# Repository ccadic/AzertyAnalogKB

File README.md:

# AzertyAnalogKB
Analogic Azerty Keyboard
KICAD Files

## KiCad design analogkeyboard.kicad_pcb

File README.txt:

Source of inspiration 
https://twitter.com/technoblogy/status/1015229517068152832

Link to source files
http://www.technoblogy.com/show?28WK

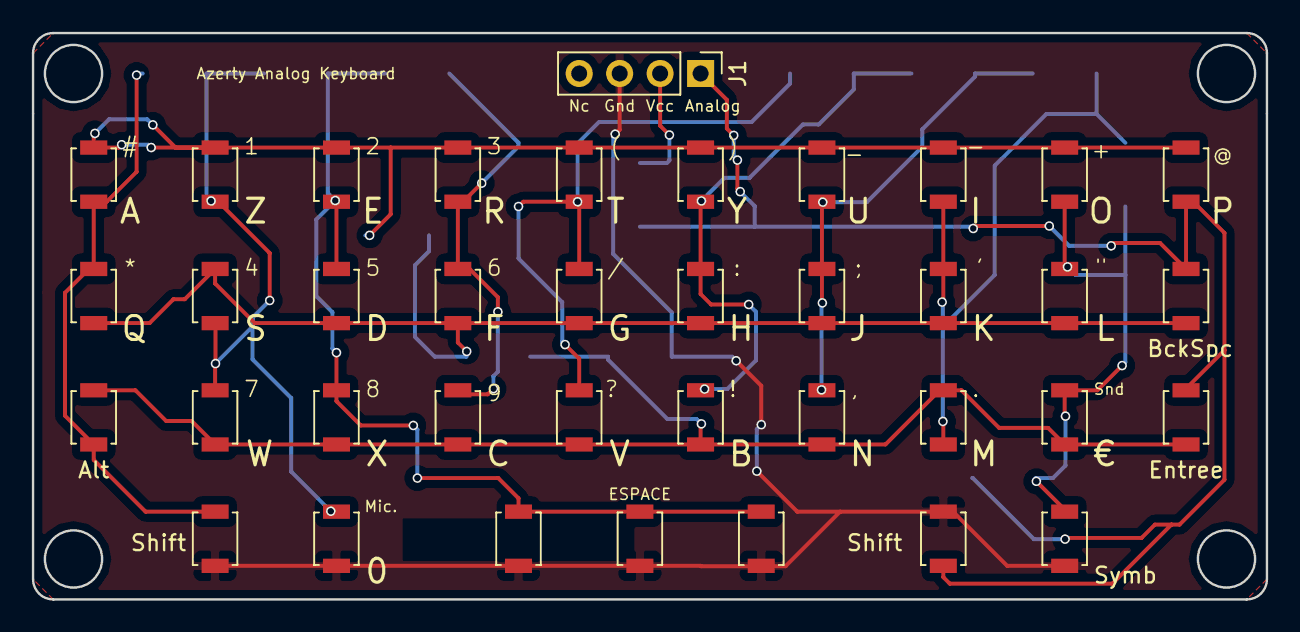
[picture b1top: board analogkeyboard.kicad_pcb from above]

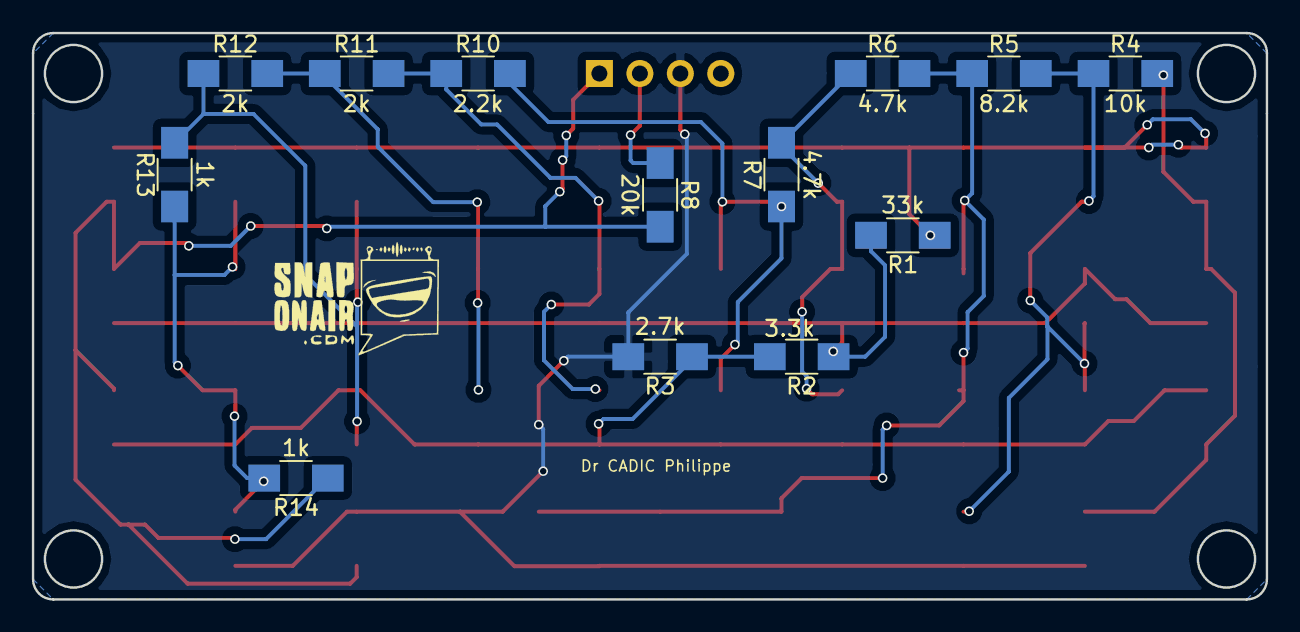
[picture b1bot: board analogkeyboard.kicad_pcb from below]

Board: 2 copper layers, 77.5 x 35.6 mm, 51 parts (13 on the bottom side), 15 nets.

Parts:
0: SW_Push_45deg; SW_SPST_B3U-1000P
A: SW_Push_45deg; SW_SPST_B3U-1000P
Alt: SW_Push_45deg; SW_SPST_B3U-1000P
B: SW_Push_45deg; SW_SPST_B3U-1000P
BckSpc: SW_Push_45deg; SW_SPST_B3U-1000P
C: SW_Push_45deg; SW_SPST_B3U-1000P
D: SW_Push_45deg; SW_SPST_B3U-1000P
E: SW_Push_45deg; SW_SPST_B3U-1000P
ESPACE: SW_Push_45deg; SW_SPST_B3U-1000P
ESPACE#2, ESPACE#3: SW_Push_45deg; SW_SPST_B3U-1000P
Entree: SW_Push_45deg; SW_SPST_B3U-1000P
F: SW_Push_45deg; SW_SPST_B3U-1000P
G: SW_Push_45deg; SW_SPST_B3U-1000P
H: SW_Push_45deg; SW_SPST_B3U-1000P
I: SW_Push_45deg; SW_SPST_B3U-1000P
J: SW_Push_45deg; SW_SPST_B3U-1000P
J1: AtinyCon; Socket_Strip_Straight_1x04_Pitch2.54mm
K: SW_Push_45deg; SW_SPST_B3U-1000P
L: SW_Push_45deg; SW_SPST_B3U-1000P
M: SW_Push_45deg; SW_SPST_B3U-1000P
N: SW_Push_45deg; SW_SPST_B3U-1000P
O: SW_Push_45deg; SW_SPST_B3U-1000P
P: SW_Push_45deg; SW_SPST_B3U-1000P
Q: SW_Push_45deg; SW_SPST_B3U-1000P
R: SW_Push_45deg; SW_SPST_B3U-1000P
R1: 33k; R_1206_HandSoldering
R2: 3.3k; R_1206_HandSoldering
R3: 2.7k; R_1206_HandSoldering
R4: 10k; R_1206_HandSoldering
R5: 8.2k; R_1206_HandSoldering
R6, R7: 4.7k; R_1206_HandSoldering
R8: 20k; R_1206_HandSoldering
R10: 2.2k; R_1206_HandSoldering
R11, R12: 2k; R_1206_HandSoldering
R13, R14: 1k; R_1206_HandSoldering
S: SW_Push_45deg; SW_SPST_B3U-1000P
Shift: SW_Push_45deg; SW_SPST_B3U-1000P
Shift#2: SW_Push_45deg; SW_SPST_B3U-1000P
Symb: SW_Push_45deg; SW_SPST_B3U-1000P
T: SW_Push_45deg; SW_SPST_B3U-1000P
U: SW_Push_45deg; SW_SPST_B3U-1000P
V: SW_Push_45deg; SW_SPST_B3U-1000P
W: SW_Push_45deg; SW_SPST_B3U-1000P
X: SW_Push_45deg; SW_SPST_B3U-1000P
Y: SW_Push_45deg; SW_SPST_B3U-1000P
Z: SW_Push_45deg; SW_SPST_B3U-1000P
€: SW_Push_45deg; SW_SPST_B3U-1000P

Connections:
Analog_Input: BckSpc.1, Entree.1, J1.1, P.1, R8.2, R14.1, Shift#2.1
GND: 0.2, ESPACE.2, ESPACE#2.2, ESPACE#3.2, J1.3, R3.2, Shift.2, Shift#2.2, Symb.2
unnamed: 0.1, R4.1, R5.2, S.1, W.1, Z.1
unnamed: A.1, Alt.1, Q.1, R4.2, Shift.1
unnamed: A.2, E.2, I.2, O.2, P.2, R.2, R1.1, T.2, U.2, Y.2, Z.2
unnamed: Alt.2, B.2, C.2, Entree.2, M.2, N.2, R2.2, R3.1, V.2, W.2, X.2, €.2
unnamed: B.1, H.1, R10.1, R11.2, Y.1
unnamed: BckSpc.2, D.2, F.2, G.2, H.2, J.2, K.2, L.2, Q.2, R1.2, R2.1, S.2
unnamed: C.1, F.1, R.1, R6.1, R7.2
unnamed: D.1, E.1, ESPACE.1, ESPACE#2.1, ESPACE#3.1, R5.1, R6.2, X.1
unnamed: L.1, O.1, R13.1, R14.2, Symb.1, €.1
unnamed: G.1, R7.1, R10.2, T.1, V.1
unnamed: I.1, K.1, M.1, R12.1, R13.2
unnamed: J.1, N.1, R11.1, R12.2, U.1
Vcc: J1.2, R8.1
